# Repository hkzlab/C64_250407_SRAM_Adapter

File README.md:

# C64 ASSY 250407 SRAM Adapter

## DISCLAIMER

Any use of this project is **under your own responsibility**.
You will be responsible of checking the correct construction and functionality of your board.
By using this project You will agree that I cannot be held responsible if it will destroy any of your devices, damage your computer, burn down your house or whatever.

**WARNING**: This is compatible with the 250407 board only!!!

## Introduction

This board implements a static RAM replacement for the DRAMs on a C64 with a 250407 motherboard.
I wanted to both reduce power consumption, and get a fix for the [VSP bug](https://www.pouet.net/prod.php?which=61024#c637759).

You will have to socket your DRAM ICs to install this board.

### Ordering the boards

You can order the board for this project at [PCBWay](https://www.pcbway.com/project/shareproject/C64_250407_SRAM_Adapter_9502264b.html) and support me or download 
the gerbers and have them printed wherever you like!!!

## Features

- You can choose to use SMD or DIP components for the logic and memory ICs
- Once the DRAMs are socketed, the board is easy to plug in and remove
- If your C64 lacks C203, a capacitor can be fitted on this board without having to further modify your motherboard

## Hardware

The board was designed with [KiCad](https://kicad.org/) EDA.

### Bill of Materials

| Component              | Qty | Type / Value                     | Notes                                                                |
| ---------------------- | --- | -------------------------------- | -------------------------------------------------------------------- |
| C1, C2, C3             |  3  | 100nF ceramic cap, SMD 1206      | Decoupling caps, rated at least 10V.                                 |
| C5                     |  1  | ~82-820pF ceramic cap, THT 2.5mm | Optional, install either this or C4 if C203 on mobo is missing       |
| C4                     |  1  | ~82-820pF ceramic cap, SMD 1206  | Optional, install either this or C5 if C203 on mobo is missing       |
| U1                     |  1  | 74HCT32, DIP14 or SO14           | Can be replaced with an ACT/ALS/LS/F. Do NOT use an HC.              |
| U2                     |  1  | 74HCT573, DIP 20 or TSSOP20      | Can be replaced with an ACT/ALS/LS/F. Do NOT use an HC.              |
| U3                     |  1  | 128Kx8 SRAM, DIP32 or SOP32      | I tested ICs between 75ns to 100ns without issue. 628128 pinout.     |
| Headers                |  1  | 40p 2.54mm machined header strip | Cut it into 4x8p, 1x2p and 5x1p pieces, then solder on the underside |

C4/C5 adjust `/CAS` timing to make the board play nice in C64s that do not have C203 fitted.

Value of C5/C4 is non critical, I had good luck with 300pF and 100pF caps. Note that I could also make do without the cap entirely
by replacing U1 (the '32 gate) with a schottky based one, so LS/ALS/F family.

### Fixes

#### Rev. 1

Rev. 1 lacks the space to solder C4/C5, you can just bodge a cap on the first two pins (`GND` and `/CAS`) of the bottom right header.

### Known Issues

I could not detect stability issues, the only problem I found is a graphical glitch on the title screen of ZetaWing 2,
where a single lines of pixels is flickering.

Note that this same issue **happens with other SRAM mods** (meant for shortboards) bodged to work on this machine, and disappears when using real DRAM ICs.

This seems a quirk of my VIC-II, a 6569R3. I modified the motherboard to support an 8565 and the issue disappeared (tested with an 8565R2).

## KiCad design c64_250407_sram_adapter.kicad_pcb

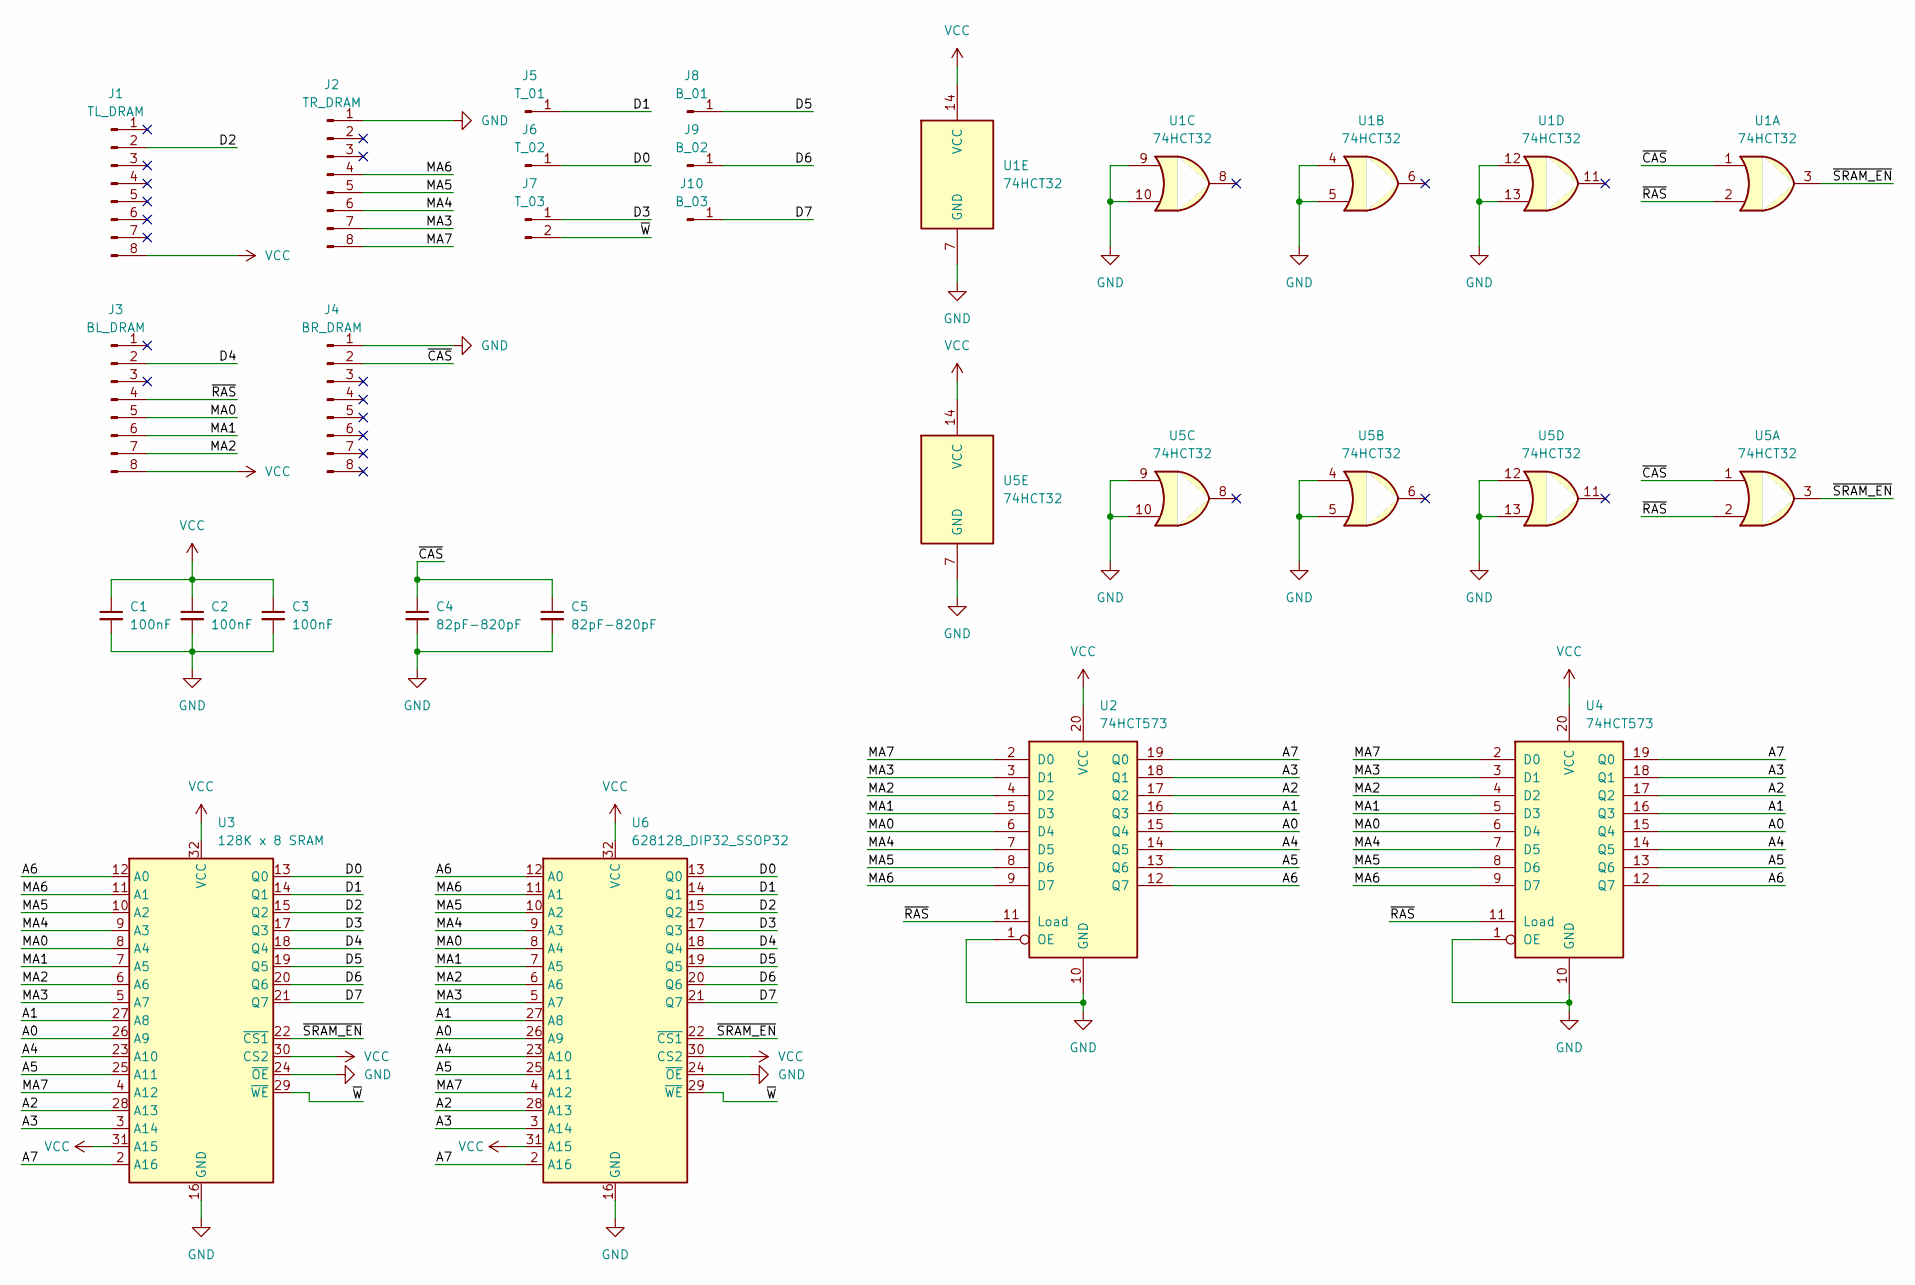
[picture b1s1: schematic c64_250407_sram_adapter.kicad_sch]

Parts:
C1, C2, C3: 100nF; C_1206_3216Metric_Pad1.33x1.80mm_HandSolder
C4: 82pF-820pF; C_1206_3216Metric_Pad1.33x1.80mm_HandSolder
C5: 82pF-820pF; C_Disc_D3.0mm_W2.0mm_P2.50mm
J1: TL_DRAM; PinHeader_1x08_P2.54mm_Vertical
J2: TR_DRAM; PinHeader_1x08_P2.54mm_Vertical
J3: BL_DRAM; PinHeader_1x08_P2.54mm_Vertical
J4: BR_DRAM; PinHeader_1x08_P2.54mm_Vertical
J5: T_01; PinHeader_1x01_P2.54mm_Vertical
J6: T_02; PinHeader_1x01_P2.54mm_Vertical
J7: T_03; PinHeader_1x02_P2.54mm_Vertical
J8: B_01; PinHeader_1x01_P2.54mm_Vertical
J9: B_02; PinHeader_1x01_P2.54mm_Vertical
J10: B_03; PinHeader_1x01_P2.54mm_Vertical
U1: 74HCT32; DIP-14_W7.62mm
U2: 74HCT573; DIP-20_W7.62mm
U3: 128K x 8 SRAM; DIP-32_W15.24mm
U4: 74HCT573; TSSOP-20_4.4x6.5mm_P0.65mm
U5: 74HCT32; SO-14_3.9x8.65mm_P1.27mm
U6: 628128_DIP32_SSOP32; SOP-32_11.305x20.495mm_P1.27mm

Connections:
/A0: U2.15 (Q4), U3.26 (A9), U4.15 (Q4), U6.26 (A9)
/A1: U2.16 (Q3), U3.27 (A8), U4.16 (Q3), U6.27 (A8)
/A2: U2.17 (Q2), U3.28 (A13), U4.17 (Q2), U6.28 (A13)
/A3: U2.18 (Q1), U3.3 (A14), U4.18 (Q1), U6.3 (A14)
/A4: U2.14 (Q5), U3.23 (A10), U4.14 (Q5), U6.23 (A10)
/A5: U2.13 (Q6), U3.25 (A11), U4.13 (Q6), U6.25 (A11)
/A6: U2.12 (Q7), U3.12 (A0), U4.12 (Q7), U6.12 (A0)
/A7: U2.19 (Q0), U3.2 (A16), U4.19 (Q0), U6.2 (A16)
/D0: J6.1, U3.13 (Q0), U6.13 (Q0)
/D1: J5.1, U3.14 (Q1), U6.14 (Q1)
/D2: J1.2, U3.15 (Q2), U6.15 (Q2)
/D3: J7.1, U3.17 (Q3), U6.17 (Q3)
/D4: J3.2, U3.18 (Q4), U6.18 (Q4)
/D5: J8.1, U3.19 (Q5), U6.19 (Q5)
/D6: J9.1, U3.20 (Q6), U6.20 (Q6)
/D7: J10.1, U3.21 (Q7), U6.21 (Q7)
/MA0: J3.5, U2.6 (D4), U3.8 (A4), U4.6 (D4), U6.8 (A4)
/MA1: J3.6, U2.5 (D3), U3.7 (A5), U4.5 (D3), U6.7 (A5)
/MA2: J3.7, U2.4 (D2), U3.6 (A6), U4.4 (D2), U6.6 (A6)
/MA3: J2.7, U2.3 (D1), U3.5 (A7), U4.3 (D1), U6.5 (A7)
/MA4: J2.6, U2.7 (D5), U3.9 (A3), U4.7 (D5), U6.9 (A3)
/MA5: J2.5, U2.8 (D6), U3.10 (A2), U4.8 (D6), U6.10 (A2)
/MA6: J2.4, U2.9 (D7), U3.11 (A1), U4.9 (D7), U6.11 (A1)
/MA7: J2.8, U2.2 (D0), U3.4 (A12), U4.2 (D0), U6.4 (A12)
/~CAS: C4.1, C5.1, J4.2, U1.1, U5.1
/~RAS: J3.4, U1.2, U2.11 (Load), U4.11 (Load), U5.2
/~SRAM_EN: U1.3, U3.22 (~CS1), U5.3, U6.22 (~CS1)
/~W: J7.2, U3.29 (~WE), U6.29 (~WE)
GND: C1.2, C2.2, C3.2, C4.2, C5.2, J2.1, J4.1, U1.4, U1.5, U1.7 (GND), U1.9, U1.10, U1.12, U1.13, U2.1 (OE), U2.10 (GND), U3.16 (GND), U3.24 (~OE), U4.1 (OE), U4.10 (GND), U5.4, U5.5, U5.7 (GND), U5.9, U5.10, U5.12, U5.13, U6.16 (GND), U6.24 (~OE)
VCC: C1.1, C2.1, C3.1, J1.8, J3.8, U1.14 (VCC), U2.20 (VCC), U3.30 (CS2), U3.31 (A15), U3.32 (VCC), U4.20 (VCC), U5.14 (VCC), U6.30 (CS2), U6.31 (A15), U6.32 (VCC)

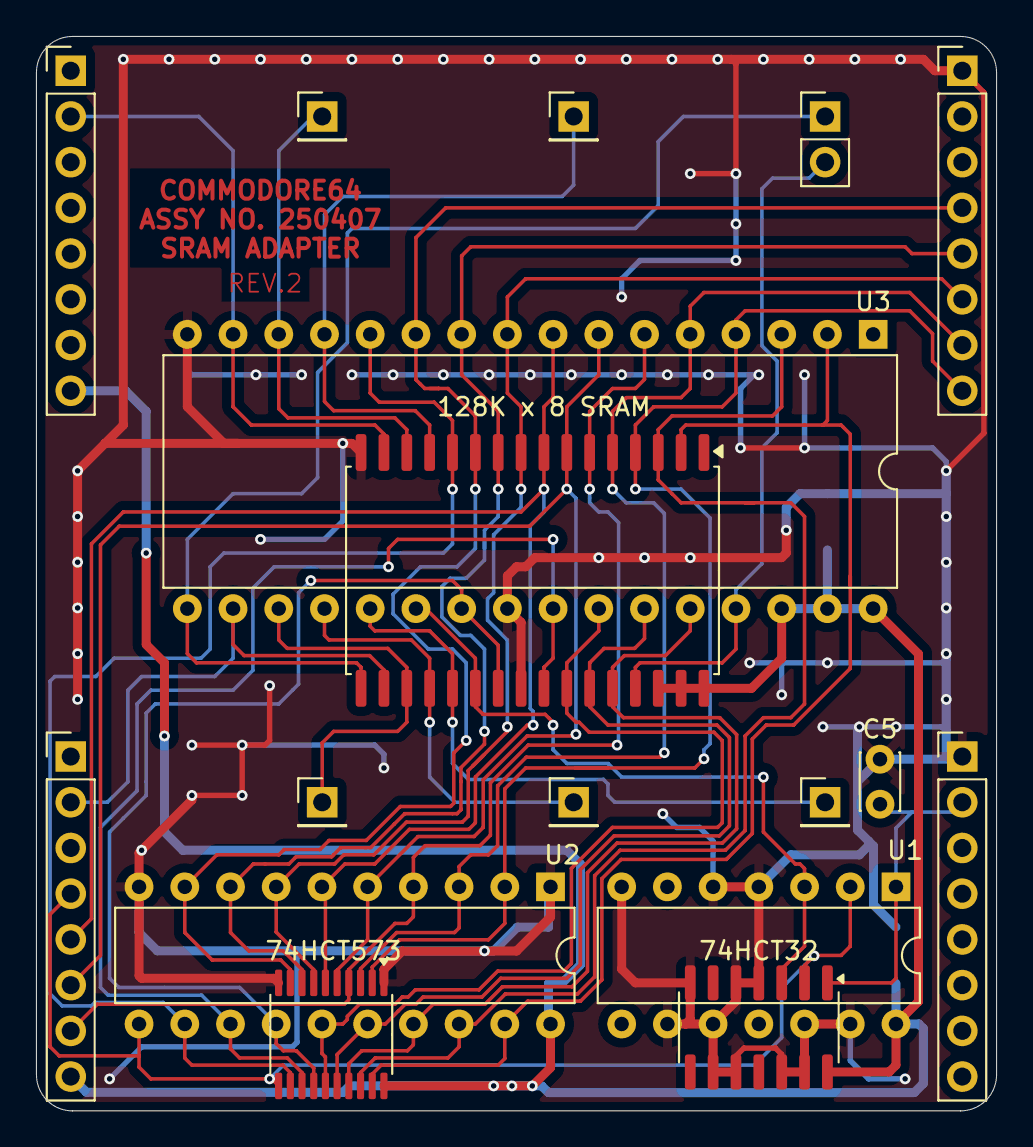
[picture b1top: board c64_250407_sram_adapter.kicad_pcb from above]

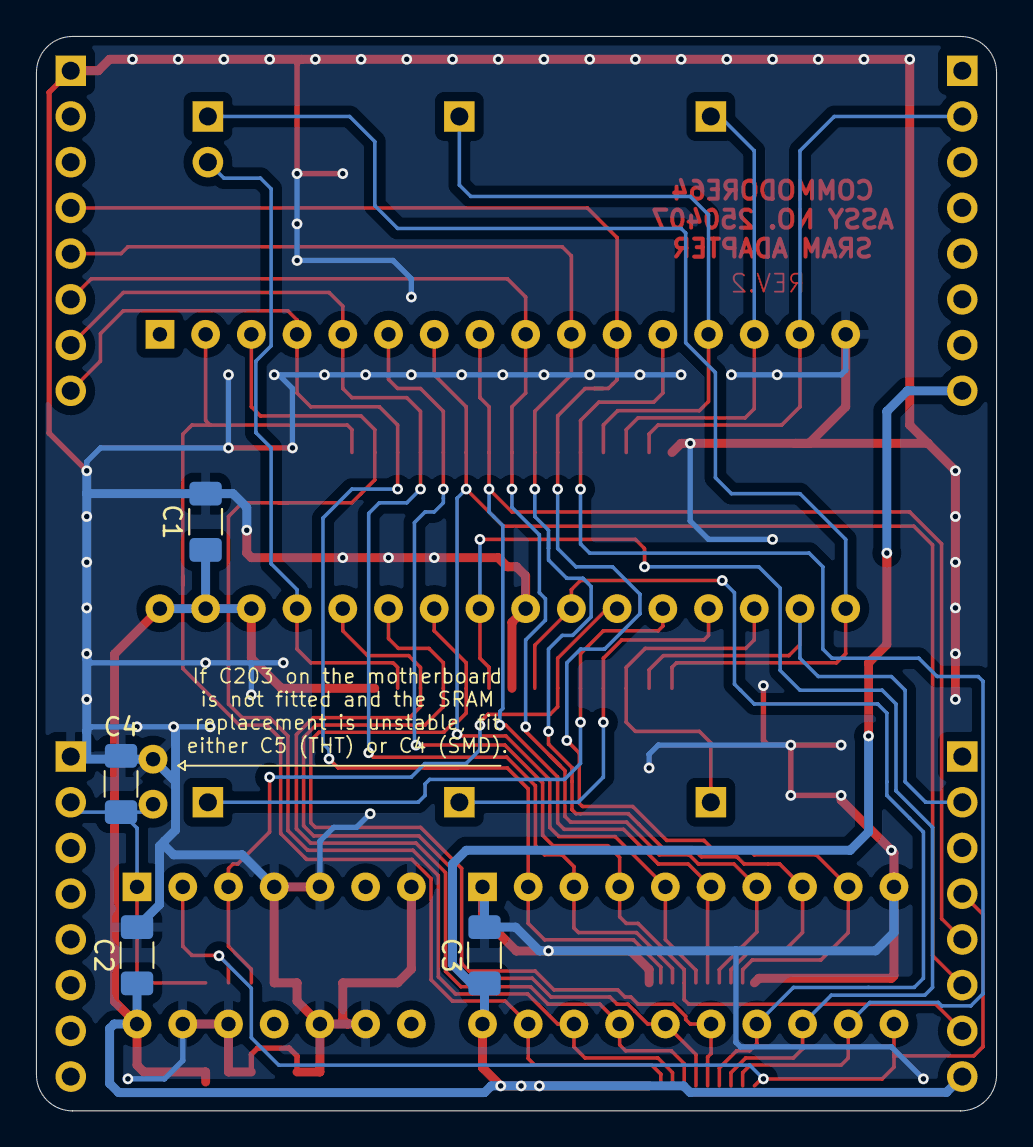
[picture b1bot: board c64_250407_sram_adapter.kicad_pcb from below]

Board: 2 copper layers, 53.3 x 59.7 mm, 21 parts (4 on the bottom side), 30 nets.

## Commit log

2024-12-29 Add sram converter
2024-12-29 Rev. 1 with better power trace
2024-12-29 Further tweak rev.1
2024-12-29 Remove useless measurement
2024-12-30 Rename files
2025-01-20 Updated PCB to rev.2, adding optional /CAS delay cap
2025-01-20 Fixed the silkscreen
2025-01-26 Fill in the readme
2025-01-26 Fix pictures
2025-01-26 Adding an additional disclaimer
2025-01-26 Small tweaks to README
2025-01-26 Add note on ordering
2025-01-26 Fix measure in readme
2025-01-27 Updated info on glitches
